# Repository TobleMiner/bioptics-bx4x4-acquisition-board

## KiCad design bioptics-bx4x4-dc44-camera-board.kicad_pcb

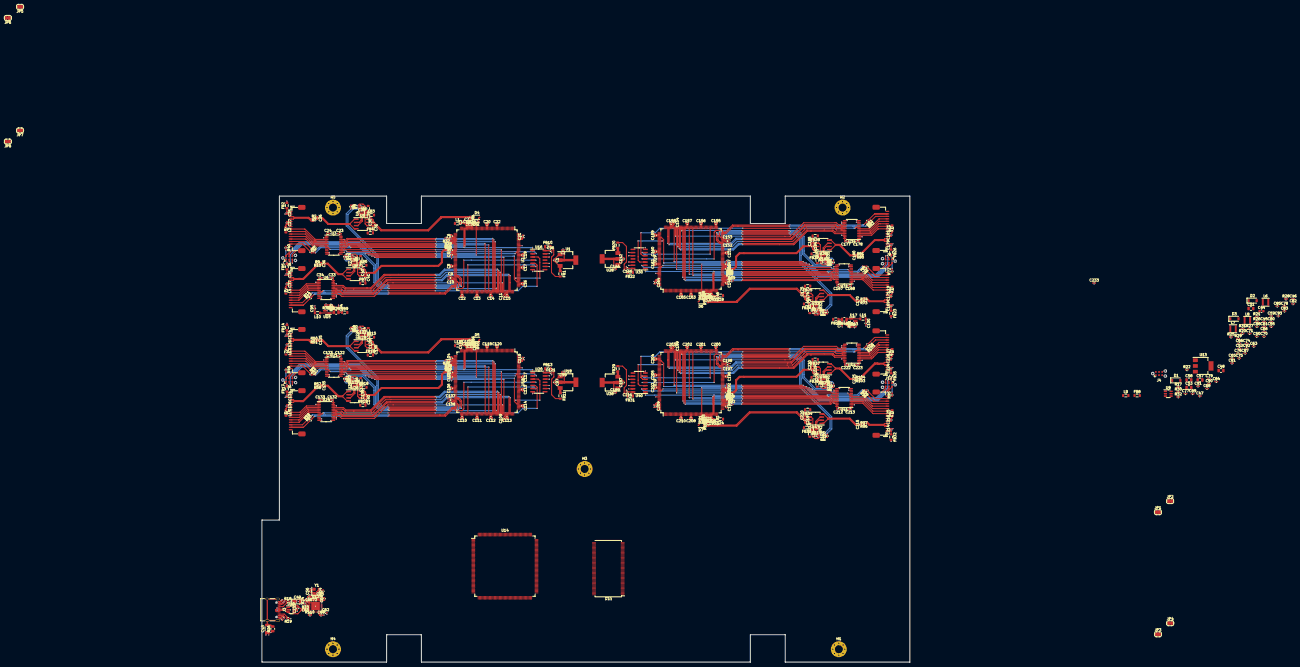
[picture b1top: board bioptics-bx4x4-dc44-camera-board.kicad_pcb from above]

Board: 4 copper layers, 260.0 x 187.0 mm, 475 parts (0 on the bottom side), 457 nets.

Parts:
C1, C18, C45, C66, C88, C94, C97, C98, C116, C142, C161, C187, C206: 1uF; C_0402_1005Metric
C2, C3, C25, C35, C70, C73, C74, C99, C101, C124, C134, C144, C146, C169, C179, C189, C191, C214, C224: 4.7uF; C_0402_1005Metric
C4, C5, C6, C7, C8, C10, C12, C13, C14, C15, C16, C17, C19, C20, C21, C22, C23, C24, C27, C28, C29, C30, C31, C33, C34, C37, C38, C39, C40, C41, C46, C47, C50, C52, C55, C59, C60, C61, C62, C63, C64, C65, C67, C68, C69, C71, C72, C75, C76, C77, C78, C80, C82, C83, C84, C85, C86, C87, C89, C90, C91, C92, C93, C95, C96, C100, C102, C103, C104, C105, C106, C108, C110, C111, C112, C113, C114, C115, C117, C118, C119, C120, C121, C122, C123, C126, C127, C128, C129, C130, C132, C133, C136, C137, C138, C139, C140, C147, C148, C149, C150, C151, C153, C155, C156, C157, C158, C159, C160, C162, C163, C164, C165, C166, C167, C168, C171, C172, C173, C174, C175, C177, C178, C181, C182, C183, C184, C185, C192, C193, C194, C195, C196, C198, C200, C201, C202, C203, C204, C205, C207, C208, C209, C210, C211, C212, C213, C216, C217, C218, C219, C220, C222, C223, C226, C227, C228, C229, C230, C232, C233, C234, C235, C236, C237: 100nF; C_0402_1005Metric
C9, C11, C79, C81, C107, C109, C152, C154, C197, C199: 2.2uF; C_0402_1005Metric
C26, C32, C36, C42, C125, C131, C135, C141, C170, C176, C180, C186, C215, C221, C225, C231: 47pF; C_0402_1005Metric
C43: 1nF; C_1206_3216Metric
C44: 22uF; C_0603_1608Metric
C48, C51, C53, C57, C58: 10uF; C_0805_2012Metric
C49: 10uF; CP_EIA-3216-10_Kemet-I
C54, C56: 20pF; C_0402_1005Metric
D1, D2, D3: B5819W; D_SOD-123
D4, D5, D6, D7: 1N4148WS; D_SOD-323
FB1, FB2, FB3, FB4, FB5, FB6, FB7, FB8, FB9, FB10, FB11, FB12, FB13, FB14, FB15, FB16, FB17, FB18, FB19, FB20, FB22, FB23, FB24, FB25, FB26, FB27, FB28, FB29, FB31, FB32, FB33, FB34, FB35, FB36, FB37: 600R@100MHz; L_0805_2012Metric
H1, H2, H3, H4, H5: MH; MountingHole_3.2mm_M3_Pad_Via
J1, J2, J7, J8, J10, J11, J13, J14: RadEye1; FC1-15-02-T-WT_P1.0mm
J3: USB_C_Receptacle_USB2.0; USB_C_Receptacle_Palconn_UTC16-G
J4, J5, J6, J9, J12: TagConnect_TC2030_SWD; Tag-Connect_TC2030-IDC-NL_2x03_P1.27mm_Vertical
JP1, JP2, JP3, JP4, JP5, JP6, JP7, JP8: SolderJumper_2_Open; SolderJumper-2_P1.3mm_Open_RoundedPad1.0x1.5mm
L1, L2, L3, L4, L5, L9, L10, L11, L12, L13, L14, L15, L16, L18, L19, L20, L21, L22, L24, L25, L26, L27, L28: 10uH; L_0805_2012Metric
L6: 4.7uH; L_Taiyo-Yuden_MD-3030
L7, L8: 100uH; L_Taiyo-Yuden_NR-30xx
R1, R20, R25, R45, R68, R91: 100k; R_0402_1005Metric
R2, R3, R4, R5, R8, R9, R10, R11, R12, R15, R32, R34, R40, R42, R49, R50, R51, R52, R53, R56, R57, R58, R59, R60, R63, R72, R73, R74, R75, R76, R79, R80, R81, R82, R83, R86, R95, R96, R97, R98, R99, R102, R103, R104, R105, R106, R109: 100; R_0402_1005Metric
R6, R7, R13, R14, R30, R31, R54, R55, R61, R62, R77, R78, R84, R85, R100, R101, R107, R108: 4.7k; R_0402_1005Metric
R16: 200k; R_0805_2012Metric
R17, R21: 20k; R_0402_1005Metric
R18, R19, R23, R33, R41, R110: 5.1k; R_0402_1005Metric
R22: 10kR; R_0402_1005Metric
R24: 12k; R_0402_1005Metric
R26, R27, R28, R29, R37, R38, R39, R46, R47, R48, R69, R70, R71, R92, R93, R94: 33; R_0402_1005Metric
R35, R43: 10k; R_0402_1005Metric
R36, R44: 120; R_0805_2012Metric
U1, U13, U18, U28, U38: AMS1117-3.3; SOT-223-3_TabPin2
U2, U14, U19, U29, U39: STM32H753IITx; LQFP-176_24x24mm_P0.5mm
U3, U6, U21, U24, U31, U34, U41, U44: SN74AVC8T245PW; TSSOP-24_4.4x7.8mm_P0.65mm
U4, U7, U22, U25, U32, U35, U42, U45: AD5112; Analog_LFCSP-8-1EP_2x2mm_P0.5mm_EP1.00x1.60mm
U5, U8, U23, U26, U33, U36, U43, U46: INA849; SOIC-8_3.9x4.9mm_P1.27mm
U9: FP6291; SOT-23-6
U10: SRV05-4; SOT-23-6
U11: IS4xS32160F-xTL; TSOP-II-86_22.2x10.16mm_P0.5mm
U12: USB3300-EZK; QFN-32-1EP_5x5mm_P0.5mm_EP3.45x3.45mm
U15, U17: CJ431; SOT-23
U16, U20, U30, U40: 7408; SO-14_3.9x8.65mm_P1.27mm
Y1: 24MHz; Crystal_SMD_3225-4Pin_3.2x2.5mm

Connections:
+3.3VA: C74.1, C77.1, C88.1, L9.2, U14.38 (VREF+), U14.39 (VDDA)
+3V3: C46.1, C47.1, C50.1, C52.1, C55.1, C59.1, C60.1, C61.1, C62.1, C63.1, C64.1, C65.1, C67.1, C68.1, C70.1, C71.1, C76.1, C78.1, C80.1, C82.1, C83.1, C84.1, C85.1, C86.1, C87.1, C89.1, C90.1, C91.1, C92.1, C93.1, C233.1, L9.1, R25.1, R30.1, R31.1, R32.1, U11.1 (VDD), U11.3 (VDDQ), U11.9 (VDDQ), U11.15 (VDD), U11.29 (VDD), U11.35 (VDDQ), U11.41 (VDDQ), U11.43 (VDD), U11.49 (VDDQ), U11.55 (VDDQ), U11.75 (VDDQ), U11.81 (VDDQ), U12.6 (VDD3.3), U12.16 (VDD3.3), U12.25 (VDD3.3), U12.30 (VDD3.3), U12.31 (REG_EN), U13.2 (VO), U14.6 (VBAT), U14.15 (VDD), U14.23 (VDD), U14.36 (VDD), U14.49 (VDD), U14.62 (VDD), U14.72 (VDD), U14.82 (VDD), U14.91 (VDD), U14.103 (VDD), U14.114 (VDD33_USB), U14.127 (VDD), U14.136 (VDD), U14.149 (VDD), U14.159 (VDD), U14.171 (PDR_ON), U14.172 (VDD), U19.142 (PD0), U29.143 (PD1), U39.142 (PD0), U39.143 (PD1)
+5V: C24.1, C34.1, C44.1, C45.2, C49.1, C123.1, C133.1, C168.1, C178.1, C213.1, C223.1, C232.1, FB1.2, FB2.2, FB5.2, FB8.2, FB9.2, FB10.2, FB11.2, FB12.2, FB13.2, FB14.2, FB17.2, FB20.2, FB22.2, FB23.2, FB26.2, FB29.2, FB31.2, FB32.2, FB35.2, J3.A4 (VBUS), J3.A9 (VBUS), J3.B4 (VBUS), J3.B9 (VBUS), L3.2, L5.2, L6.1, L14.2, L16.2, L20.2, L22.2, L26.2, L28.2, R23.2, U3.1 (VCCA), U6.1 (VCCA), U9.4 (EN), U9.5 (VCC), U10.5 (VP), U21.1 (VCCA), U24.1 (VCCA), U31.1 (VCCA), U34.1 (VCCA), U41.1 (VCCA), U44.1 (VCCA)
+8V: C58.2, FB3.2, FB6.2, FB15.2, FB18.2, FB24.2, FB27.2, FB33.2, FB36.2, L8.2
-8V: C57.2, FB4.1, FB7.1, FB16.1, FB19.1, FB25.1, FB28.1, FB34.1, FB37.1, L7.2
/3v8_1: C95.1, L2.2, L4.2, L10.2, L13.2, L15.2
/3v8_2: C100.1, L11.2, L19.2, L21.2, L25.2, L27.2
/D+: J3.A6 (D+), J3.B6 (D+), U10.1 (IO1), U12.7 (DP)
/D-: J3.A7 (D-), J3.B7 (D-), U10.3 (IO2), U12.8 (DM)
/FMC_A0: U11.25 (A0), U14.16 (PF0)
/FMC_A1: U11.26 (A1), U14.17 (PF1)
/FMC_A2: U11.27 (A2), U14.18 (PF2)
/FMC_A3: U11.60 (A3), U14.19 (PF3)
/FMC_A4: U11.61 (A4), U14.20 (PF4)
/FMC_A5: U11.62 (A5), U14.21 (PF5)
/FMC_A6: U11.63 (A6), U14.60 (PF12)
/FMC_A7: U11.64 (A7), U14.63 (PF13)
/FMC_A8: U11.65 (A8), U14.64 (PF14)
/FMC_A9: U11.66 (A9), U14.65 (PF15)
/FMC_A10: U11.24 (A10), U14.66 (PG0)
/FMC_A11: U11.21 (A11), U14.67 (PG1)
/FMC_A12: U11.69 (A12), U14.106 (PG2)
/FMC_A14: U11.22 (BA0), U14.108 (PG4)
/FMC_A15: U11.23 (BA1), U14.109 (PG5)
/FMC_D0: U11.2 (DQ0), U14.104 (PD14)
/FMC_D1: U11.4 (DQ1), U14.105 (PD15)
/FMC_D2: U11.5 (DQ2), U14.142 (PD0)
/FMC_D3: U11.7 (DQ3), U14.143 (PD1)
/FMC_D4: U11.8 (DQ4), U14.68 (PE7)
/FMC_D5: U11.10 (DQ5), U14.69 (PE8)
/FMC_D6: U11.11 (DQ6), U14.70 (PE9)
/FMC_D7: U11.13 (DQ7), U14.73 (PE10)
/FMC_D8: U11.74 (DQ8), U14.74 (PE11)
/FMC_D9: U11.76 (DQ9), U14.75 (PE12)
/FMC_D10: U11.77 (DQ10), U14.76 (PE13)
/FMC_D11: U11.79 (DQ11), U14.77 (PE14)
/FMC_D12: U11.80 (DQ12), U14.78 (PE15)
/FMC_D13: U11.82 (DQ13), U14.96 (PD8)
/FMC_D14: U11.83 (DQ14), U14.97 (PD9)
/FMC_D15: U11.85 (DQ15), U14.98 (PD10)
/FMC_D16: U11.31 (DQ16), U14.85 (PH8)
/FMC_D17: U11.33 (DQ17), U14.86 (PH9)
/FMC_D18: U11.34 (DQ18), U14.87 (PH10)
/FMC_D19: U11.36 (DQ19), U14.88 (PH11)
/FMC_D20: U11.37 (DQ20), U14.89 (PH12)
/FMC_D21: U11.39 (DQ21), U14.128 (PH13)
/FMC_D22: U11.40 (DQ22), U14.129 (PH14)
/FMC_D23: U11.42 (DQ23), U14.130 (PH15)
/FMC_D24: U11.45 (DQ24), U14.131 (PI0)
/FMC_D25: U11.47 (DQ25), U14.132 (PI1)
/FMC_D26: U11.48 (DQ26), U14.133 (PI2)
/FMC_D27: U11.50 (DQ27), U14.134 (PI3)
/FMC_D28: U11.51 (DQ28), U14.175 (PI6)
/FMC_D29: U11.53 (DQ29), U14.176 (PI7)
/FMC_D30: U11.54 (DQ30), U14.11 (PI9)
/FMC_D31: U11.56 (DQ31), U14.12 (PI10)
/FMC_NBL0: U11.16 (DQM0), U14.169 (PE0)
/FMC_NBL1: U11.71 (DQM1), U14.170 (PE1)
/FMC_NBL2: U11.28 (DQM2), U14.173 (PI4)
/FMC_NBL3: U11.59 (DQM3), U14.174 (PI5)
/FMC_SDCKE0: U11.67 (CKE), U14.43 (PH2)
/FMC_SDCLK: U11.68 (CLK), U14.112 (PG8)
/FMC_SDNCAS: U11.18 (~CAS), U14.160 (PG15)
/FMC_SDNE0: U11.20 (~CS), U14.44 (PH3)
/FMC_SDNRAS: U11.19 (~RAS), U14.59 (PF11)
/FMC_SDNWE: U11.17 (~WE), U14.46 (PH5)
/I2C_SCL: R30.2, U2.167 (PB8), U14.164 (PB6), U19.167 (PB8), U29.167 (PB8), U39.167 (PB8)
/I2C_SDA: R31.2, U2.165 (PB7), U14.165 (PB7), U19.165 (PB7), U29.165 (PB7), U39.165 (PB7)
/IMAGE_CLK_{1}: R39.2, U14.25 (PF7)
/IMAGE_CLK_{2}: R48.2, U14.156 (PG13)
/IMAGE_CLK_{3}: R71.2, U14.1 (PE2)
/IMAGE_CLK_{4}: R94.2, U14.145 (PD3)
/IMAGE_MISO_{1}: R27.1, U2.52 (PA6)
/IMAGE_MISO_{2}: R26.1, U19.52 (PA6)
/IMAGE_MISO_{3}: R29.1, U29.52 (PA6)
/IMAGE_MISO_{4}: R28.1, U39.52 (PA6)
/IMAGE_MOSI_{1}: R38.2, U14.27 (PF9)
/IMAGE_MOSI_{2}: R47.2, U14.157 (PG14)
/IMAGE_MOSI_{3}: R70.2, U14.5 (PE6)
/IMAGE_MOSI_{4}: R93.2, U14.95 (PB15)
/IMAGE_~FRAME_{1}: R37.2, U14.24 (PF6)
/IMAGE_~FRAME_{2}: R46.2, U14.147 (PD5)
/IMAGE_~FRAME_{3}: R69.2, U14.3 (PE4)
/IMAGE_~FRAME_{4}: R92.2, U14.122 (PA11)
/IO0_{1}: U2.163 (PB5), U14.29 (PH0)
/IO0_{2}: U14.2 (PE3), U19.163 (PB5)
/IO0_{3}: U14.123 (PA12), U29.163 (PB5)
/IO0_{4}: U14.8 (PC13), U39.163 (PB5)
/IO1_{1}: U2.164 (PB6), U14.54 (PC4)
/IO1_{2}: U14.55 (PC5), U19.164 (PB6)
/IO1_{3}: U14.146 (PD4), U29.164 (PB6)
/IO1_{4}: U14.150 (PD6), U39.164 (PB6)
/IRQ_{1}: U2.168 (PB9), U14.58 (PB2)
/IRQ_{2}: U14.111 (PG7), U19.168 (PB9)
/IRQ_{3}: U14.7 (PI8), U29.168 (PB9)
/IRQ_{4}: U14.33 (PC1), U39.168 (PB9)
/MCU_~RST: C75.1, J4.3 (~RESET), R25.2, U14.31 (NRST)
/SLAVE_CLK: U2.29 (PH0), U14.119 (PA8), U19.29 (PH0), U29.29 (PH0), U39.29 (PH0)
/SLAVE_~RST: D4.1 (K), D5.1 (K), D6.1 (K), D7.1 (K)
/Sensor board 1/3v3: C2.1, C4.1, C6.1, C8.1, C10.1, C12.1, C13.1, C14.1, C15.1, C16.1, C17.1, C19.1, C20.1, C21.1, C22.1, C23.2, C28.2, C33.2, C38.2, C234.1, L1.1, R1.1, R6.1, R7.1, R13.1, R14.1, R40.1, U1.2 (VO), U2.15 (VDD), U2.23 (VDD), U2.36 (VDD), U2.49 (VDD), U2.62 (VDD), U2.72 (VDD), U2.82 (VDD), U2.91 (VDD), U2.103 (VDD), U2.114 (VDD33_USB), U2.127 (VDD), U2.136 (VDD), U2.149 (VDD), U2.159 (VDD), U2.171 (PDR_ON), U2.172 (VDD), U3.23 (VCCB), U3.24 (VCCB), U4.8 (V_{LOGIC}), U6.23 (VCCB), U6.24 (VCCB), U7.8 (V_{LOGIC})
/Sensor board 1/3v3A: C3.1, C7.1, C18.1, L1.2, U2.38 (VREF+), U2.39 (VDDA)
/Sensor board 1/ADC1_TRIG_IN: U2.140 (PC11), U16.3
/Sensor board 1/ADC1_TRIG_OUT: U2.122 (PA11), U3.16 (B6)
/Sensor board 1/ADC3_TRIG_IN: U2.95 (PB15), U16.6
/Sensor board 1/ADC3_TRIG_OUT: U2.123 (PA12), U6.16 (B6)
/Sensor board 1/BIN_{1}: U2.109 (PG5), U3.18 (B4)
/Sensor board 1/BIN_{2}: U2.128 (PH13), U6.18 (B4)
/Sensor board 1/CLOCK_{1}: U2.117 (PC8), U3.19 (B3)
/Sensor board 1/CLOCK_{2}: U2.121 (PA10), U6.19 (B3)
/Sensor board 1/FRAME_{1}: R4.2, U2.40 (PA0)
/Sensor board 1/FRAME_{2}: R11.2, U2.87 (PH10)
/Sensor board 1/JTDO: J5.6 (SWO), U2.161 (PB3)
/Sensor board 1/LINE_{1}: R5.2, U2.41 (PA1), U16.1
/Sensor board 1/LINE_{2}: R12.2, U2.88 (PH11), U16.4
/Sensor board 1/MCUL_~RST: C5.1, D4.2 (A), J5.3 (~RESET), R1.2, U2.31 (NRST)
/Sensor board 1/NDR_{1}: U2.112 (PG8), U3.17 (B5)
/Sensor board 1/NDR_{2}: U2.129 (PH14), U6.17 (B5)
/Sensor board 1/RESET_{1}: U2.115 (PC6), U3.21 (B1)
/Sensor board 1/RESET_{2}: U2.119 (PA8), U6.21 (B1)
/Sensor board 1/SCL_{1}: R6.2, U2.79 (PB10), U4.6 (SCL)
/Sensor board 1/SCL_{2}: R13.2, U2.84 (PH7), U7.6 (SCL)
/Sensor board 1/SDA_{1}: R7.2, U2.80 (PB11), U4.7 (SDA)
/Sensor board 1/SDA_{2}: R14.2, U2.118 (PC9), U7.7 (SDA)
/Sensor board 1/START_{1}: U2.116 (PC7), U3.20 (B2)
/Sensor board 1/START_{2}: U2.120 (PA9), U6.20 (B2)
/Sensor board 1/Sensor 1/BIN_{5V}: J1.11, U3.6 (A4)
/Sensor board 1/Sensor 1/CLOCK_{5V}: J1.10, U3.5 (A3)
/Sensor board 1/Sensor 1/FRAME_{5V}: J1.13, R4.1
/Sensor board 1/Sensor 1/LINE_{5V}: J1.14, R5.1
/Sensor board 1/Sensor 1/NDR_{5V}: J1.12, U3.7 (A5)
/Sensor board 1/Sensor 1/RESET_{5V}: J1.8, U3.3 (A1)
/Sensor board 1/Sensor 1/S+: C26.2, R2.2, U5.4 (+)
/Sensor board 1/Sensor 1/S-: C26.1, R3.1, U5.1 (-)
/Sensor board 1/Sensor 1/START_{5V}: J1.9, U3.4 (A2)
/Sensor board 1/Sensor 1/TRIG_OUT_{5V}: U3.8 (A6), U16.2
/Sensor board 1/Sensor 2/BIN_{5V}: J2.11, U6.6 (A4)
/Sensor board 1/Sensor 2/CLOCK_{5V}: J2.10, U6.5 (A3)
/Sensor board 1/Sensor 2/FRAME_{5V}: J2.13, R11.1
/Sensor board 1/Sensor 2/LINE_{5V}: J2.14, R12.1
/Sensor board 1/Sensor 2/NDR_{5V}: J2.12, U6.7 (A5)
/Sensor board 1/Sensor 2/RESET_{5V}: J2.8, U6.3 (A1)
/Sensor board 1/Sensor 2/S+: C36.2, R9.2, U8.4 (+)
/Sensor board 1/Sensor 2/S-: C36.1, R10.1, U8.1 (-)
/Sensor board 1/Sensor 2/START_{5V}: J2.9, U6.4 (A2)
/Sensor board 1/Sensor 2/TRIG_OUT_{5V}: U6.8 (A6), U16.5
/Sensor board 1/sensor1_out: C32.2, R8.2, U2.35 (PC3_C)
/Sensor board 1/sensor2_out: C42.2, R15.2, U2.59 (PF11)
/Sensor board 2/3v3: C99.1, C102.1, C104.1, C106.1, C108.1, C110.1, C111.1, C112.1, C113.1, C114.1, C115.1, C117.1, C118.1, C119.1, C120.1, C122.2, C127.2, C132.2, C137.2, C235.1, L12.1, R45.1, R49.1, R54.1, R55.1, R61.1, R62.1, U18.2 (VO), U19.15 (VDD), U19.23 (VDD), U19.36 (VDD), U19.49 (VDD), U19.62 (VDD), U19.72 (VDD), U19.82 (VDD), U19.91 (VDD), U19.103 (VDD), U19.114 (VDD33_USB), U19.127 (VDD), U19.136 (VDD), U19.149 (VDD), U19.159 (VDD), U19.171 (PDR_ON), U19.172 (VDD), U21.23 (VCCB), U21.24 (VCCB), U22.8 (V_{LOGIC}), U24.23 (VCCB), U24.24 (VCCB), U25.8 (V_{LOGIC})
/Sensor board 2/3v3A: C101.1, C105.1, C116.1, L12.2, U19.38 (VREF+), U19.39 (VDDA)
/Sensor board 2/ADC1_TRIG_IN: U19.140 (PC11), U20.3
/Sensor board 2/ADC1_TRIG_OUT: U19.122 (PA11), U21.16 (B6)
/Sensor board 2/ADC3_TRIG_IN: U19.95 (PB15), U20.6
/Sensor board 2/ADC3_TRIG_OUT: U19.123 (PA12), U24.16 (B6)
/Sensor board 2/BIN_{1}: U19.109 (PG5), U21.18 (B4)
/Sensor board 2/BIN_{2}: U19.128 (PH13), U24.18 (B4)
/Sensor board 2/CLOCK_{1}: U19.117 (PC8), U21.19 (B3)
/Sensor board 2/CLOCK_{2}: U19.121 (PA10), U24.19 (B3)
/Sensor board 2/FRAME_{1}: R52.2, U19.40 (PA0)
/Sensor board 2/FRAME_{2}: R59.2, U19.87 (PH10)
/Sensor board 2/JTDO: J6.6 (SWO), U19.161 (PB3)
/Sensor board 2/LINE_{1}: R53.2, U19.41 (PA1), U20.1
/Sensor board 2/LINE_{2}: R60.2, U19.88 (PH11), U20.4
/Sensor board 2/MCUL_~RST: C103.1, D5.2 (A), J6.3 (~RESET), R45.2, U19.31 (NRST)
/Sensor board 2/NDR_{1}: U19.112 (PG8), U21.17 (B5)
/Sensor board 2/NDR_{2}: U19.129 (PH14), U24.17 (B5)
/Sensor board 2/RESET_{1}: U19.115 (PC6), U21.21 (B1)
/Sensor board 2/RESET_{2}: U19.119 (PA8), U24.21 (B1)
/Sensor board 2/SCL_{1}: R54.2, U19.79 (PB10), U22.6 (SCL)
/Sensor board 2/SCL_{2}: R61.2, U19.84 (PH7), U25.6 (SCL)
/Sensor board 2/SDA_{1}: R55.2, U19.80 (PB11), U22.7 (SDA)
/Sensor board 2/SDA_{2}: R62.2, U19.118 (PC9), U25.7 (SDA)
/Sensor board 2/START_{1}: U19.116 (PC7), U21.20 (B2)
/Sensor board 2/START_{2}: U19.120 (PA9), U24.20 (B2)
/Sensor board 2/Sensor 1/BIN_{5V}: J7.11, U21.6 (A4)
/Sensor board 2/Sensor 1/CLOCK_{5V}: J7.10, U21.5 (A3)
/Sensor board 2/Sensor 1/FRAME_{5V}: J7.13, R52.1
/Sensor board 2/Sensor 1/LINE_{5V}: J7.14, R53.1
/Sensor board 2/Sensor 1/NDR_{5V}: J7.12, U21.7 (A5)
/Sensor board 2/Sensor 1/RESET_{5V}: J7.8, U21.3 (A1)
/Sensor board 2/Sensor 1/S+: C125.2, R50.2, U23.4 (+)
/Sensor board 2/Sensor 1/S-: C125.1, R51.1, U23.1 (-)
/Sensor board 2/Sensor 1/START_{5V}: J7.9, U21.4 (A2)
/Sensor board 2/Sensor 1/TRIG_OUT_{5V}: U20.2, U21.8 (A6)
/Sensor board 2/Sensor 2/BIN_{5V}: J8.11, U24.6 (A4)
/Sensor board 2/Sensor 2/CLOCK_{5V}: J8.10, U24.5 (A3)
/Sensor board 2/Sensor 2/FRAME_{5V}: J8.13, R59.1
/Sensor board 2/Sensor 2/LINE_{5V}: J8.14, R60.1
/Sensor board 2/Sensor 2/NDR_{5V}: J8.12, U24.7 (A5)
/Sensor board 2/Sensor 2/RESET_{5V}: J8.8, U24.3 (A1)
/Sensor board 2/Sensor 2/S+: C135.2, R57.2, U26.4 (+)
/Sensor board 2/Sensor 2/S-: C135.1, R58.1, U26.1 (-)
/Sensor board 2/Sensor 2/START_{5V}: J8.9, U24.4 (A2)
/Sensor board 2/Sensor 2/TRIG_OUT_{5V}: U20.5, U24.8 (A6)
/Sensor board 2/sensor1_out: C131.2, R56.2, U19.35 (PC3_C)
/Sensor board 2/sensor2_out: C141.2, R63.2, U19.59 (PF11)
/Sensor board 3/3v3: C144.1, C147.1, C149.1, C151.1, C153.1, C155.1, C156.1, C157.1, C158.1, C159.1, C160.1, C162.1, C163.1, C164.1, C165.1, C167.2, C172.2, C177.2, C182.2, C236.1, L18.1, R68.1, R72.1, R77.1, R78.1, R84.1, R85.1, U28.2 (VO), U29.15 (VDD), U29.23 (VDD), U29.36 (VDD), U29.49 (VDD), U29.62 (VDD), U29.72 (VDD), U29.82 (VDD), U29.91 (VDD), U29.103 (VDD), U29.114 (VDD33_USB), U29.127 (VDD), U29.136 (VDD), U29.149 (VDD), U29.159 (VDD), U29.171 (PDR_ON), U29.172 (VDD), U31.23 (VCCB), U31.24 (VCCB), U32.8 (V_{LOGIC}), U34.23 (VCCB), U34.24 (VCCB), U35.8 (V_{LOGIC})
/Sensor board 3/3v3A: C146.1, C150.1, C161.1, L18.2, U29.38 (VREF+), U29.39 (VDDA)
/Sensor board 3/ADC1_TRIG_IN: U29.140 (PC11), U30.3
/Sensor board 3/ADC1_TRIG_OUT: U29.122 (PA11), U31.16 (B6)
/Sensor board 3/ADC3_TRIG_IN: U29.95 (PB15), U30.6
/Sensor board 3/ADC3_TRIG_OUT: U29.123 (PA12), U34.16 (B6)
/Sensor board 3/BIN_{1}: U29.109 (PG5), U31.18 (B4)
/Sensor board 3/BIN_{2}: U29.128 (PH13), U34.18 (B4)
/Sensor board 3/CLOCK_{1}: U29.117 (PC8), U31.19 (B3)
/Sensor board 3/CLOCK_{2}: U29.121 (PA10), U34.19 (B3)
/Sensor board 3/FRAME_{1}: R75.2, U29.40 (PA0)
/Sensor board 3/FRAME_{2}: R82.2, U29.87 (PH10)
/Sensor board 3/JTDO: J9.6 (SWO), U29.161 (PB3)
/Sensor board 3/LINE_{1}: R76.2, U29.41 (PA1), U30.1
/Sensor board 3/LINE_{2}: R83.2, U29.88 (PH11), U30.4
/Sensor board 3/MCUL_~RST: C148.1, D6.2 (A), J9.3 (~RESET), R68.2, U29.31 (NRST)
/Sensor board 3/NDR_{1}: U29.112 (PG8), U31.17 (B5)
/Sensor board 3/NDR_{2}: U29.129 (PH14), U34.17 (B5)
/Sensor board 3/RESET_{1}: U29.115 (PC6), U31.21 (B1)
/Sensor board 3/RESET_{2}: U29.119 (PA8), U34.21 (B1)
/Sensor board 3/SCL_{1}: R77.2, U29.79 (PB10), U32.6 (SCL)
/Sensor board 3/SCL_{2}: R84.2, U29.84 (PH7), U35.6 (SCL)
/Sensor board 3/SDA_{1}: R78.2, U29.80 (PB11), U32.7 (SDA)
/Sensor board 3/SDA_{2}: R85.2, U29.118 (PC9), U35.7 (SDA)
/Sensor board 3/START_{1}: U29.116 (PC7), U31.20 (B2)
/Sensor board 3/START_{2}: U29.120 (PA9), U34.20 (B2)
/Sensor board 3/Sensor 1/BIN_{5V}: J10.11, U31.6 (A4)
/Sensor board 3/Sensor 1/CLOCK_{5V}: J10.10, U31.5 (A3)
/Sensor board 3/Sensor 1/FRAME_{5V}: J10.13, R75.1
/Sensor board 3/Sensor 1/LINE_{5V}: J10.14, R76.1
/Sensor board 3/Sensor 1/NDR_{5V}: J10.12, U31.7 (A5)
/Sensor board 3/Sensor 1/RESET_{5V}: J10.8, U31.3 (A1)
/Sensor board 3/Sensor 1/S+: C170.2, R73.2, U33.4 (+)
/Sensor board 3/Sensor 1/S-: C170.1, R74.1, U33.1 (-)
/Sensor board 3/Sensor 1/START_{5V}: J10.9, U31.4 (A2)
/Sensor board 3/Sensor 1/TRIG_OUT_{5V}: U30.2, U31.8 (A6)
/Sensor board 3/Sensor 2/BIN_{5V}: J11.11, U34.6 (A4)
/Sensor board 3/Sensor 2/CLOCK_{5V}: J11.10, U34.5 (A3)
/Sensor board 3/Sensor 2/FRAME_{5V}: J11.13, R82.1
/Sensor board 3/Sensor 2/LINE_{5V}: J11.14, R83.1
/Sensor board 3/Sensor 2/NDR_{5V}: J11.12, U34.7 (A5)
/Sensor board 3/Sensor 2/RESET_{5V}: J11.8, U34.3 (A1)
/Sensor board 3/Sensor 2/S+: C180.2, R80.2, U36.4 (+)
/Sensor board 3/Sensor 2/S-: C180.1, R81.1, U36.1 (-)
/Sensor board 3/Sensor 2/START_{5V}: J11.9, U34.4 (A2)
/Sensor board 3/Sensor 2/TRIG_OUT_{5V}: U30.5, U34.8 (A6)
/Sensor board 3/sensor1_out: C176.2, R79.2, U29.35 (PC3_C)
/Sensor board 3/sensor2_out: C186.2, R86.2, U29.59 (PF11)
/Sensor board 4/3v3: C189.1, C192.1, C194.1, C196.1, C198.1, C200.1, C201.1, C202.1, C203.1, C204.1, C205.1, C207.1, C208.1, C209.1, C210.1, C212.2, C217.2, C222.2, C227.2, C237.1, L24.1, R91.1, R95.1, R100.1, R101.1, R107.1, R108.1, U38.2 (VO), U39.15 (VDD), U39.23 (VDD), U39.36 (VDD), U39.49 (VDD), U39.62 (VDD), U39.72 (VDD), U39.82 (VDD), U39.91 (VDD), U39.103 (VDD), U39.114 (VDD33_USB), U39.127 (VDD), U39.136 (VDD), U39.149 (VDD), U39.159 (VDD), U39.171 (PDR_ON), U39.172 (VDD), U41.23 (VCCB), U41.24 (VCCB), U42.8 (V_{LOGIC}), U44.23 (VCCB), U44.24 (VCCB), U45.8 (V_{LOGIC})
/Sensor board 4/3v3A: C191.1, C195.1, C206.1, L24.2, U39.38 (VREF+), U39.39 (VDDA)
/Sensor board 4/ADC1_TRIG_IN: U39.140 (PC11), U40.3
/Sensor board 4/ADC1_TRIG_OUT: U39.122 (PA11), U41.16 (B6)
/Sensor board 4/ADC3_TRIG_IN: U39.95 (PB15), U40.6
/Sensor board 4/ADC3_TRIG_OUT: U39.123 (PA12), U44.16 (B6)
/Sensor board 4/BIN_{1}: U39.109 (PG5), U41.18 (B4)
/Sensor board 4/BIN_{2}: U39.128 (PH13), U44.18 (B4)
/Sensor board 4/CLOCK_{1}: U39.117 (PC8), U41.19 (B3)
/Sensor board 4/CLOCK_{2}: U39.121 (PA10), U44.19 (B3)
/Sensor board 4/FRAME_{1}: R98.2, U39.40 (PA0)
/Sensor board 4/FRAME_{2}: R105.2, U39.87 (PH10)
/Sensor board 4/JTDO: J12.6 (SWO), U39.161 (PB3)
/Sensor board 4/LINE_{1}: R99.2, U39.41 (PA1), U40.1
/Sensor board 4/LINE_{2}: R106.2, U39.88 (PH11), U40.4
/Sensor board 4/MCUL_~RST: C193.1, D7.2 (A), J12.3 (~RESET), R91.2, U39.31 (NRST)
/Sensor board 4/NDR_{1}: U39.112 (PG8), U41.17 (B5)
/Sensor board 4/NDR_{2}: U39.129 (PH14), U44.17 (B5)
/Sensor board 4/RESET_{1}: U39.115 (PC6), U41.21 (B1)
/Sensor board 4/RESET_{2}: U39.119 (PA8), U44.21 (B1)
/Sensor board 4/SCL_{1}: R100.2, U39.79 (PB10), U42.6 (SCL)
/Sensor board 4/SCL_{2}: R107.2, U39.84 (PH7), U45.6 (SCL)
/Sensor board 4/SDA_{1}: R101.2, U39.80 (PB11), U42.7 (SDA)
/Sensor board 4/SDA_{2}: R108.2, U39.118 (PC9), U45.7 (SDA)
/Sensor board 4/START_{1}: U39.116 (PC7), U41.20 (B2)
/Sensor board 4/START_{2}: U39.120 (PA9), U44.20 (B2)
/Sensor board 4/Sensor 1/BIN_{5V}: J13.11, U41.6 (A4)
/Sensor board 4/Sensor 1/CLOCK_{5V}: J13.10, U41.5 (A3)
/Sensor board 4/Sensor 1/FRAME_{5V}: J13.13, R98.1
/Sensor board 4/Sensor 1/LINE_{5V}: J13.14, R99.1
/Sensor board 4/Sensor 1/NDR_{5V}: J13.12, U41.7 (A5)
/Sensor board 4/Sensor 1/RESET_{5V}: J13.8, U41.3 (A1)
/Sensor board 4/Sensor 1/S+: C215.2, R96.2, U43.4 (+)
/Sensor board 4/Sensor 1/S-: C215.1, R97.1, U43.1 (-)
/Sensor board 4/Sensor 1/START_{5V}: J13.9, U41.4 (A2)
/Sensor board 4/Sensor 1/TRIG_OUT_{5V}: U40.2, U41.8 (A6)
/Sensor board 4/Sensor 2/BIN_{5V}: J14.11, U44.6 (A4)
/Sensor board 4/Sensor 2/CLOCK_{5V}: J14.10, U44.5 (A3)
/Sensor board 4/Sensor 2/FRAME_{5V}: J14.13, R105.1
/Sensor board 4/Sensor 2/LINE_{5V}: J14.14, R106.1
/Sensor board 4/Sensor 2/NDR_{5V}: J14.12, U44.7 (A5)
/Sensor board 4/Sensor 2/RESET_{5V}: J14.8, U44.3 (A1)
/Sensor board 4/Sensor 2/S+: C225.2, R103.2, U46.4 (+)
/Sensor board 4/Sensor 2/S-: C225.1, R104.1, U46.1 (-)
/Sensor board 4/Sensor 2/START_{5V}: J14.9, U44.4 (A2)
/Sensor board 4/Sensor 2/TRIG_OUT_{5V}: U40.5, U44.8 (A6)
/Sensor board 4/sensor1_out: C221.2, R102.2, U39.35 (PC3_C)
/Sensor board 4/sensor2_out: C231.2, R109.2, U39.59 (PF11)
/ULPI_CK: U12.14 (CLKOUT), U14.51 (PA5)
/ULPI_D0: U12.24 (DATA0), U14.47 (PA3)
/ULPI_D1: U12.23 (DATA1), U14.56 (PB0)
/ULPI_D2: U12.22 (DATA2), U14.57 (PB1)
/ULPI_D3: U12.21 (DATA3), U14.79 (PB10)
/ULPI_D4: U12.20 (DATA4), U14.80 (PB11)
/ULPI_D5: U12.19 (DATA5), U14.92 (PB12)
/ULPI_D6: U12.18 (DATA6), U14.93 (PB13)
/ULPI_D7: U12.17 (DATA7), U14.163 (PB5)
/ULPI_DIR: U12.12 (DIR), U14.13 (PI11)
/ULPI_NXT: U12.11 (NXT), U14.45 (PH4)
/ULPI_STP: U12.13 (STP), U14.32 (PC0)
GND: C1.1, C2.2, C3.2, C4.2, C5.2, C6.2, C7.2, C8.2, C9.1, C10.2, C11.1, C12.2, C13.2, C14.2, C15.2, C16.2, C17.2, C18.2, C19.2, C20.2, C21.2, C22.2, C23.1, C24.2, C25.2, C27.1, C28.1, C29.2, C30.1, C31.1, C32.1, C33.1, C34.2, C35.2, C37.1, C38.1, C39.2, C40.1, C41.1, C42.1, C43.1, C44.2, C45.1, C46.2, C47.2, C49.2, C50.2, C51.1, C52.2, C53.1, C54.1, C55.2, C56.2, C57.1, C58.1, C59.2, C60.2, C61.2, C62.2, C63.2, C64.2, C65.2, C66.1, C67.2, C68.2, C69.2, C70.2, C71.2, C72.2, C73.2, C74.2, C75.2, C76.2, C77.2, C78.2, C79.1, C80.2, C81.1, C82.2, C83.2, C84.2, C85.2, C86.2, C87.2, C88.2, C89.2, C90.2, C91.2, C92.2, C93.2, C94.1, C95.2, C96.2, C97.1, C98.1, C99.2, C100.2, C101.2, C102.2, C103.2, C104.2, C105.2, C106.2, C107.1, C108.2, C109.1, C110.2, C111.2, C112.2, C113.2, C114.2, C115.2, C116.2, C117.2, C118.2, C119.2, C120.2, C121.2, C122.1, C123.2, C124.2, C126.1, C127.1, C128.2, C129.1, C130.1, C131.1, C132.1, C133.2, C134.2, C136.1, C137.1, C138.2, C139.1, C140.1, C141.1, C142.1, C144.2, C146.2, C147.2, C148.2, C149.2, C150.2, C151.2, C152.1, C153.2, C154.1, C155.2, C156.2, C157.2, C158.2, C159.2, C160.2, C161.2, C162.2, C163.2, C164.2, C165.2, C166.2, C167.1, C168.2, C169.2, C171.1, C172.1, C173.2, C174.1, C175.1, C176.1, C177.1, C178.2, C179.2, C181.1, C182.1, C183.2, C184.1, C185.1, C186.1, C187.1, C189.2, C191.2, C192.2, C193.2, C194.2, C195.2, C196.2, C197.1, C198.2, C199.1, C200.2, C201.2, C202.2, C203.2, C204.2, C205.2, C206.2, C207.2, C208.2, C209.2, C210.2, C211.2, C212.1, C213.2, C214.2, C216.1, C217.1, C218.2, C219.1, C220.1, C221.1, C222.1, C223.2, C224.2, C226.1, C227.1, C228.2, C229.1, C230.1, C231.1, C232.2, C233.2, C234.2, C235.2, C236.2, C237.2, D1.1 (K), H1.1, H2.1, H3.1, H4.1, H5.1, J1.2, J1.5, J1.7, J1.15, J1.MP (MountPin), J2.2, J2.5, J2.7, J2.15, J2.MP (MountPin), J3.A1 (GND), J3.A12 (GND), J3.B1 (GND), J3.B12 (GND), J4.5 (GND), J5.5 (GND), J6.5 (GND), J7.2, J7.5, J7.7, J7.15, J7.MP (MountPin), J8.2, J8.5, J8.7, J8.15, J8.MP (MountPin), J9.5 (GND), J10.2, J10.5, J10.7, J10.15, J10.MP (MountPin), J11.2, J11.5, J11.7, J11.15, J11.MP (MountPin), J12.5 (GND), J13.2, J13.5, J13.7, J13.15, J13.MP (MountPin), J14.2, J14.5, J14.7, J14.15, J14.MP (MountPin), R16.1, R17.1, R18.2, R19.1, R22.2, R24.1, R35.2, R43.2, R110.1, U1.1 (GND), U2.14 (VSS), U2.22 (VSS), U2.34 (PC2_C), U2.37 (VSSA), U2.48 (VSS), U2.60 (PF12), U2.61 (VSS), U2.71 (VSS), U2.90 (VSS), U2.102 (VSS), U2.113 (VSS), U2.126 (VSS), U2.135 (VSS), U2.142 (PD0), U2.143 (PD1), U2.148 (VSS), U2.158 (VSS), U2.166 (BOOT0), U3.2 (DIR), U3.11 (GND), U3.12 (GND), U3.13 (GND), U3.14 (B8), U3.15 (B7), U3.22 (~OE), U4.5 (GND), U5.6 (Ref), U6.2 (DIR), U6.11 (GND), U6.12 (GND), U6.13 (GND), U6.14 (B8), U6.15 (B7), U6.22 (~OE), U7.5 (GND), U8.6 (Ref), U9.2 (GND), U10.2 (VN), U11.6 (VSSQ), U11.12 (VSSQ), U11.32 (VSSQ), U11.38 (VSSQ), U11.44 (VSS), U11.46 (VSSQ), U11.52 (VSSQ), U11.58 (VSS), U11.72 (VSS), U11.78 (VSSQ), U11.84 (VSSQ), U11.86 (VSS), U12.1 (GND), U12.2 (GND), U12.33 (GND), U13.1 (GND), U14.14 (VSS), U14.22 (VSS), U14.37 (VSSA), U14.48 (VSS), U14.61 (VSS), U14.71 (VSS), U14.90 (VSS), U14.102 (VSS), U14.113 (VSS), U14.126 (VSS), U14.135 (VSS), U14.148 (VSS), U14.158 (VSS), U14.166 (BOOT0), U15.3 (A), U16.7 (Gnd), U16.9, U16.10, U16.12, U16.13, U17.3 (A), U18.1 (GND), U19.14 (VSS), U19.22 (VSS), U19.34 (PC2_C), U19.37 (VSSA), U19.48 (VSS), U19.60 (PF12), U19.61 (VSS), U19.71 (VSS), U19.90 (VSS), U19.102 (VSS), U19.113 (VSS), U19.126 (VSS), U19.135 (VSS), U19.143 (PD1), U19.148 (VSS), U19.158 (VSS), U19.166 (BOOT0), U20.7 (Gnd), U20.9, U20.10, U20.12, U20.13, U21.2 (DIR), U21.11 (GND), U21.12 (GND), U21.13 (GND), U21.14 (B8), U21.15 (B7), U21.22 (~OE), U22.5 (GND), U23.6 (Ref), U24.2 (DIR), U24.11 (GND), U24.12 (GND), U24.13 (GND), U24.14 (B8), U24.15 (B7), U24.22 (~OE), U25.5 (GND), U26.6 (Ref), U28.1 (GND), U29.14 (VSS), U29.22 (VSS), U29.34 (PC2_C), U29.37 (VSSA), U29.48 (VSS), U29.60 (PF12), U29.61 (VSS), U29.71 (VSS), U29.90 (VSS), U29.102 (VSS), U29.113 (VSS), U29.126 (VSS), U29.135 (VSS), U29.142 (PD0), U29.148 (VSS), U29.158 (VSS), U29.166 (BOOT0), U30.7 (Gnd), U30.9, U30.10, U30.12, U30.13, U31.2 (DIR), U31.11 (GND), U31.12 (GND), U31.13 (GND), U31.14 (B8), U31.15 (B7), U31.22 (~OE), U32.5 (GND), U33.6 (Ref), U34.2 (DIR), U34.11 (GND), U34.12 (GND), U34.13 (GND), U34.14 (B8), U34.15 (B7), U34.22 (~OE), U35.5 (GND), U36.6 (Ref), U38.1 (GND), U39.14 (VSS), U39.22 (VSS), U39.34 (PC2_C), U39.37 (VSSA), U39.48 (VSS), U39.60 (PF12), U39.61 (VSS), U39.71 (VSS), U39.90 (VSS), U39.102 (VSS), U39.113 (VSS), U39.126 (VSS), U39.135 (VSS), U39.148 (VSS), U39.158 (VSS), U39.166 (BOOT0), U40.7 (Gnd), U40.9, U40.10, U40.12, U40.13, U41.2 (DIR), U41.11 (GND), U41.12 (GND), U41.13 (GND), U41.14 (B8), U41.15 (B7), U41.22 (~OE), U42.5 (GND), U43.6 (Ref), U44.2 (DIR), U44.11 (GND), U44.12 (GND), U44.13 (GND), U44.14 (B8), U44.15 (B7), U44.22 (~OE), U45.5 (GND), U46.6 (Ref), Y1.2, Y1.4
unnamed: C1.2, FB1.1, U1.3 (VI)
unnamed: C9.2, U2.81 (VCAP1)
unnamed: C11.2, U2.125 (VCAP2)
unnamed: C25.1, FB2.1, J1.1
unnamed: C27.2, J1.6, L2.1
unnamed: C29.1, L3.1, U4.1 (VDD)
unnamed: C30.2, FB3.1, U5.8 (V+)
unnamed: C31.2, FB4.2, U5.5 (V-)
unnamed: C35.1, FB5.1, J2.1
unnamed: C37.2, J2.6, L4.1
unnamed: C39.1, L5.1, U7.1 (VDD)
unnamed: C40.2, FB6.1, U8.8 (V+)
unnamed: C41.2, FB7.2, U8.5 (V-)
unnamed: C43.2, J3.S1 (SHIELD), R16.2
unnamed: C48.1, D2.2 (A), L6.2, U9.1 (LX)
unnamed: C48.2, D1.2 (A), D3.1 (K)
unnamed: C51.2, D2.1 (K), L8.1, R20.1
unnamed: C53.2, D3.2 (A), L7.1
unnamed: C54.2, U12.27 (XO), Y1.3
unnamed: C56.1, U12.28 (XI), Y1.1
unnamed: C66.2, FB8.1, U13.3 (VI)
unnamed: C69.1, C73.1, U12.15 (VDD1.8), U12.26 (VDD1.8)
unnamed: C72.1, U12.29 (VDDA1.8)
unnamed: C79.2, U14.81 (VCAP1)
unnamed: C81.2, U14.125 (VCAP2)
unnamed: C94.2, FB9.1, R36.2
unnamed: C97.2, FB11.1, U18.3 (VI)
unnamed: C98.2, FB12.1, R44.2
unnamed: C107.2, U19.81 (VCAP1)
unnamed: C109.2, U19.125 (VCAP2)
unnamed: C124.1, FB14.1, J7.1
unnamed: C126.2, J7.6, L13.1
unnamed: C128.1, L14.1, U22.1 (VDD)
unnamed: C129.2, FB15.1, U23.8 (V+)
unnamed: C130.2, FB16.2, U23.5 (V-)
unnamed: C134.1, FB17.1, J8.1
unnamed: C136.2, J8.6, L15.1
unnamed: C138.1, L16.1, U25.1 (VDD)
unnamed: C139.2, FB18.1, U26.8 (V+)
unnamed: C140.2, FB19.2, U26.5 (V-)
unnamed: C142.2, FB20.1, U28.3 (VI)
unnamed: C152.2, U29.81 (VCAP1)
unnamed: C154.2, U29.125 (VCAP2)
unnamed: C169.1, FB23.1, J10.1
unnamed: C171.2, J10.6, L19.1
unnamed: C173.1, L20.1, U32.1 (VDD)
unnamed: C174.2, FB24.1, U33.8 (V+)
unnamed: C175.2, FB25.2, U33.5 (V-)
unnamed: C179.1, FB26.1, J11.1
unnamed: C181.2, J11.6, L21.1
unnamed: C183.1, L22.1, U35.1 (VDD)
unnamed: C184.2, FB27.1, U36.8 (V+)
unnamed: C185.2, FB28.2, U36.5 (V-)
unnamed: C187.2, FB29.1, U38.3 (VI)
unnamed: C197.2, U39.81 (VCAP1)
unnamed: C199.2, U39.125 (VCAP2)
unnamed: C214.1, FB32.1, J13.1
unnamed: C216.2, J13.6, L25.1
unnamed: C218.1, L26.1, U42.1 (VDD)
unnamed: C219.2, FB33.1, U43.8 (V+)
unnamed: C220.2, FB34.2, U43.5 (V-)
unnamed: C224.1, FB35.1, J14.1
unnamed: C226.2, J14.6, L27.1
unnamed: C228.1, L28.1, U45.1 (VDD)
unnamed: C229.2, FB36.1, U46.8 (V+)
unnamed: C230.2, FB37.2, U46.5 (V-)
unnamed: J1.3, R2.1
unnamed: J1.4, R3.2
unnamed: J2.3, R9.1
unnamed: J2.4, R10.2
unnamed: J3.A5 (CC1), R18.1
unnamed: J3.B5 (CC2), R19.2
unnamed: J4.1 (VTGT), R32.2
unnamed: J4.2 (SWDIO), U14.124 (PA13)
unnamed: J4.4 (SWCLK), U14.137 (PA14)
unnamed: J4.6 (SWO), U14.161 (PB3)
unnamed: J5.1 (VTGT), R40.2
unnamed: J5.2 (SWDIO), JP1.1 (A), U2.124 (PA13)
unnamed: J5.4 (SWCLK), JP2.1 (A), U2.137 (PA14)
unnamed: J6.1 (VTGT), R49.2
unnamed: J6.2 (SWDIO), JP3.1 (A), U19.124 (PA13)
unnamed: J6.4 (SWCLK), JP4.1 (A), U19.137 (PA14)
unnamed: J7.3, R50.1
unnamed: J7.4, R51.2
unnamed: J8.3, R57.1
unnamed: J8.4, R58.2
unnamed: J9.1 (VTGT), R72.2
unnamed: J9.2 (SWDIO), JP5.1 (A), U29.124 (PA13)
unnamed: J9.4 (SWCLK), JP6.1 (A), U29.137 (PA14)
unnamed: J10.3, R73.1
unnamed: J10.4, R74.2
unnamed: J11.3, R80.1
unnamed: J11.4, R81.2
unnamed: J12.1 (VTGT), R95.2
unnamed: J12.2 (SWDIO), JP7.1 (A), U39.124 (PA13)
unnamed: J12.4 (SWCLK), JP8.1 (A), U39.137 (PA14)
unnamed: J13.3, R96.1
unnamed: J13.4, R97.2
unnamed: J14.3, R103.1
unnamed: J14.4, R104.2
unnamed: L10.1, R33.1, R36.1, U15.1 (K)
unnamed: L11.1, R41.1, R44.1, U17.1 (K)
unnamed: R8.1, U5.7
unnamed: R15.1, U8.7
unnamed: R17.2, U9.6 (OC)
unnamed: R20.2, R21.1
unnamed: R21.2, R22.1, U9.3 (FB)
unnamed: R23.1, U12.4 (VBUS)
unnamed: R24.2, U12.32 (RBIAS)
unnamed: R26.2, U14.155 (PG12)
unnamed: R27.2, U14.26 (PF8)
unnamed: R28.2, U14.94 (PB14)
unnamed: R29.2, U14.4 (PE5)
unnamed: R33.2, R34.1
unnamed: R34.2, R35.1, U15.2 (REF)
unnamed: R37.1, U2.50 (PA4)
unnamed: R38.1, U2.53 (PA7)
unnamed: R39.1, U2.51 (PA5)
unnamed: R41.2, R42.1
unnamed: R42.2, R43.1, U17.2 (REF)
unnamed: R46.1, U19.50 (PA4)
unnamed: R47.1, U19.53 (PA7)
unnamed: R48.1, U19.51 (PA5)
unnamed: R56.1, U23.7
unnamed: R63.1, U26.7
unnamed: R69.1, U29.50 (PA4)
unnamed: R70.1, U29.53 (PA7)
unnamed: R71.1, U29.51 (PA5)
unnamed: R79.1, U33.7
unnamed: R86.1, U36.7
unnamed: R92.1, U39.50 (PA4)
unnamed: R93.1, U39.53 (PA7)
unnamed: R94.1, U39.51 (PA5)
unnamed: R102.1, U43.7
unnamed: R109.1, U46.7
unnamed: R110.2, U12.9 (RESET)
unnamed: U4.2 (A), U5.2 (Rg)
unnamed: U4.3 (W), U5.3 (Rg)
unnamed: U7.2 (A), U8.2 (Rg)
unnamed: U7.3 (W), U8.3 (Rg)
unnamed: U22.2 (A), U23.2 (Rg)
unnamed: U22.3 (W), U23.3 (Rg)
unnamed: U25.2 (A), U26.2 (Rg)
unnamed: U25.3 (W), U26.3 (Rg)
unnamed: U32.2 (A), U33.2 (Rg)
unnamed: U32.3 (W), U33.3 (Rg)
unnamed: U35.2 (A), U36.2 (Rg)
unnamed: U35.3 (W), U36.3 (Rg)
unnamed: U42.2 (A), U43.2 (Rg)
unnamed: U42.3 (W), U43.3 (Rg)
unnamed: U45.2 (A), U46.2 (Rg)
unnamed: U45.3 (W), U46.3 (Rg)
Vcc: C96.1, C121.1, C166.1, C211.1, FB10.1, FB13.1, FB22.1, FB31.1, U16.14 (Vcc), U20.14 (Vcc), U30.14 (Vcc), U40.14 (Vcc)

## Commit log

2022-01-23 Add IS4xR32160F-xTL symbol and footprint
2022-01-23 Wire DRAM
2022-01-23 Map out available SPIs
2022-01-23 Eliminate duplicate MCU signals
2022-01-25 lib: fix clearances on Analog Devices LFCSP-8 package
2022-01-25 lib: add FP6291 step-up regulator
2022-01-25 Add RadEye1 sensor reference voltage supply
2022-01-25 Annotate components
2022-01-25 Include Feeling Tech switch mode converter library to symbol library table
2022-01-25 Add USB HS and bipolar analog power supply
2022-01-25 Setup PCB design rules
2022-01-29 lib: fix IS4xS32160F-xTL pinout
    Pin 9 was a VSSQ pin but is supposed to be VDDQ.
2022-01-29 Fix shifted FMC D30 and D31 on main STM32
    Pins for D30 and D31 were shifted up by one pin
2022-01-29 Add FC1-15-02-T-WT connetor footprint
2022-01-29 Use FC1-15-02-T-WT connector for RadEye1 modules
2022-01-29 First acquisition channel layout WiP
2022-02-05 Decouple MCU resets via diode
2022-02-05 Layout first sensor pair
2022-02-05 Use two instead of four 3.8V voltage references
2022-02-05 Fix broken SPI net labels
2022-02-05 Center snsor MCU between sensor connectors
2022-02-05 Layout remaining sensors
2022-02-06 Layout USB connector area
2022-02-07 Add sensor board power planes
